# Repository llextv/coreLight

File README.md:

# CoreLight

CoreLight is an open-source DIY lighting controller built around an STM32H743.

The project is designed to manage stage lighting systems with up to **13 DMX universes**, Ethernet protocols such as **Art-Net and sACN**, timecode synchronization, show playback and system monitoring.

The goal is not to recreate a grandMA3 console. CoreLight is intended to be a hardware platform for a future open-source lighting-control system.

## Main features

- Up to 13 DMX outputs
- DMX512 and RS-485 communication
- Art-Net and sACN support
- Planned RDM support
- LTC and MTC timecode
- Show recording and playback
- Standalone operation
- DMX routing and merging
- Failover and redundancy
- Ethernet and OSC control
- Internal web interface
- Temperature, power and fan monitoring
- MicroSD and Flash storage
- USB-C for programming and updates
- RTC with battery backup
- Custom 4-layer PCB
- 3D-printed rack-mount enclosure

Most of these features are still under development. The current version should be considered a hardware prototype rather than a finished lighting controller.

---

## Architecture

The STM32H743 is the central processor of the system. It handles network communication, timecode, DMX processing, show playback and system monitoring.

The controller can also receive LTC, MTC and external event inputs. Lighting data is processed by the STM32 and sent to the required DMX outputs.

---

## Hardware

The current design uses the following main components:

| Component | Function |
|---|---|
| **STM32H743ZIT6** | Main microcontroller |
| **W5500** | Ethernet interface |
| **MAX3485** | DMX / RS-485 transceivers |
| **CD74HC4067M** | Signal routing and multiplexing |
| **IS42S16400J-7TL** | External SDRAM |
| **W25Q128JVSIQ** | SPI Flash |
| **DS3231M+** | Real-time clock |
| **INA226AIDGST** | Power monitoring |
| **TMP117AIDRVR** | Temperature monitoring |
| **SM712** | DMX transient protection |
| **USBLC6-2SC6** | USB ESD protection |

The complete component list is available in [BOM.csv](BOM.csv).

---

## Processing and memory

The STM32H743 was selected because the project requires more processing power and memory bandwidth than a basic microcontroller-based DMX interface.

It is responsible for:

- Art-Net, sACN and OSC communication
- DMX universe management
- RDM and DMX monitoring
- Show playback
- Timecode processing
- Failover logic
- Fan and thermal management
- System logs and diagnostics

### External SDRAM

The external SDRAM is used for temporary runtime data such as:

- DMX buffers
- Network packets
- Show playback data
- Large processing structures

### SPI Flash

The W25Q128JVSIQ Flash can be used for firmware, configuration and persistent system data.

### MicroSD card

The microSD card is intended for user-accessible files:

```text
/show
/config
/logs
/firmware
```

Shows, configuration files, logs and firmware updates can be stored on the card.

---

## DMX

CoreLight is designed to support up to **13 DMX universes**.

Each output uses a MAX3485 RS-485 transceiver and includes transient protection. A DMX universe contains up to 512 channels, giving a theoretical total of:

\[
13 \times 512 = 6656 \text{ DMX channels}
\]

Standard DMX wiring is used

The DMX data rate is 250 kbit/s.

Planned DMX features include:

- Flexible universe routing
- DMX repeater mode
- RDM
- DMX monitoring
- Signal-loss detection
- DMX merging and failover

For example, one network universe could be sent to several physical outputs

---

## Art-Net, sACN and Ethernet

Ethernet communication is handled by the W5500.

The network interface is intended to support:

- Art-Net
- sACN
- OSC
- Web-based configuration and monitoring

Network universes can be mapped to any of the physical DMX outputs instead of being permanently assigned to a single port.

---

## Timecode

CoreLight includes an LTC input and is designed to support MTC.

Timecode can be used to trigger lighting events or control show playback:

Example events could include scene changes, effect triggers or the start of a complete lighting sequence.

The RTC is used for system time, logs and scheduled events. It is separate from LTC, which is used for show synchronization.

---

## Standalone playback

A show can be uploaded to the microSD card and played back without a permanent computer connection.

A show file may contain:

- Scenes
- Cues
- DMX values
- Timing information
- Events
- Timecode positions

During playback, the STM32 loads the required data and generates the DMX output in real time.

---

## Failover and DMX merging

One of the main objectives is to improve system reliability during shows.

CoreLight is intended to detect problems such as:

- Loss of network data
- Software or hardware failure
- Missing DMX input
- Communication errors

Depending on the final firmware, the controller could switch to a backup source or continue playback using a locally stored show.

DMX merging is also planned, allowing several sources to contribute to the same output:

The merging rules and failover behavior are still being designed.

---

## Monitoring and cooling

The system includes temperature and power monitoring using a TMP117 and an INA226.

The firmware will be able to control the cooling fan and warn the user in case of excessive temperature or abnormal power consumption.

Available hardware includes:

- Temperature sensor
- Power monitor
- Fan output
- Status LEDs
- Buzzer

---

## Power supply

The controller is designed for a 24 V DC input.

The regulated voltages power the STM32, Ethernet interface, DMX transceivers, sensors and other logic circuits.

---

## User interface and web interface

The initial local interface consists of:

- Rotary encoder
- Push buttons
- Status LEDs
- Buzzer

A future web interface will provide access to:

- System status
- DMX monitoring
- Network settings
- Show management
- Logs
- Temperature and power data
- Firmware updates

The controller is intended to be configurable from a browser without requiring a dedicated screen.

Software link for the moment: 
https://www.qlcplus.org/download#

---

## PCB and enclosure

The PCB was designed in KiCad and uses four layers to simplify routing and provide dedicated ground and power planes.

The board contains:

- STM32H743
- External SDRAM
- SPI Flash
- Ethernet
- 13 DMX interfaces
- LTC input
- USB-C
- MicroSD
- RTC
- Power regulation
- Monitoring circuits
- User interface connections

The current design contains approximately 192 footprints.

The enclosure is a custom 3D-printed rack-mount case with openings for the DMX outputs, Ethernet, USB-C, LTC, power, fan and user controls.

Assembly file: [coreLightAssembly.step](cad/coreLightAssembly.step)

CAD files are available in:

```text
/cad
```

The complete KiCad schematic is available in:

```text
/scheme
```

---

## Estimated cost

The current estimate is:

```text
Components:  $66.01
PCB:         $36.99
Total:      ~$103 USD
```

This does not include shipping, assembly, enclosure parts or future design changes.

---

## Project journal

The development process is documented in [JOURNAL.md](JOURNAL.md).

It includes the PCB design, STM32CubeMX configuration, KiCad work, enclosure design, BOM creation and the problems encountered during development.

---

## Inspiration

CoreLight was inspired by professional lighting hardware such as the grandMA3 Processing Unit and Replay Unit.

The project is independent and is not affiliated with MA Lighting.

- [MA Lighting grandMA3 Processing Unit](https://www.malighting.com/product/grandma3-processing-unit-m-4010510/)
- [MA Lighting grandMA3 Replay Unit](https://www.malighting.com/product/grandma3-replay-unit-4010507/)

---

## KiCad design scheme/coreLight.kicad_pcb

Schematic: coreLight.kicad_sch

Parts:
BT1: Battery; BatteryHolder_Keystone_3000_1x12mm
BZ1: Buzzer 3.3V; Buzzer_12x9.5RM7.6
C1, C4, C6, C9, C13, C16, C27, C29, C30, C31, C34, C36, C39, C42, C44, C46, C48, C50, C52, C54, C56, C58, C60, C62, C64, C66, C68, C69, C71, C72, C76, C78, C79: 100nF; C_0805_2012Metric
C2, C3, C32, C33: 22pF; C_0805_2012Metric
C5, C7, C8, C28, C35, C40, C41, C43, C45, C47, C49, C51, C53, C55, C57, C59, C61, C63, C65, C75, C77: 4.7µF; C_0805_2012Metric
C12, C81: 1uF; C_0805_2012Metric
C26, C70: 10uF; C_0805_2012Metric
C37, C67: 4.7uF; C_0805_2012Metric
C73, C74: 10nF; C_0805_2012Metric
C80: 2.2nF; C_0805_2012Metric
D4: D_TVS_Dual_AAC; D_SOT-23
D17: 1N5819; D_DO-41_SOD81_P10.16mm_Horizontal
D31, D33, D34, D35, D36, D37, D38, D39, D40, D41, D42, D43, D44: SM712; D_SOT-23
D32: 1N4148; D_DO-35_SOD27_P7.62mm_Horizontal
D47, D48, D49, D50, D51, D52, D53: LED; LED_0805_2012Metric
F2: Fuse 3-5A; Fuse_1812_4532Metric_Pad1.30x3.40mm_HandSolder
FB1, FB3: FerriteBead; C_0805_2012Metric
J1: Micro_SD_Card; microSD_HC_Hirose_DM3D-SF
J3: RJ45_Hanrun_HR911105A_Horizontal
J5, J6, J21, J23, J24, J25, J26, J27, J28, J29, J30, J31, J32: Con DMX; JST_XH_B3B-XH-A_1x03_P2.50mm_Vertical
J16: USB_C_Receptacle_USB2.0_16P; USB_C_Receptacle_HRO_TYPE-C-31-M-12
J17: 24v in; TerminalBlock_Phoenix_MKDS-1,5-2-5.08_1x02_P5.08mm_Horizont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
J18: FAN; JST_XH_B2B-XH-A_1x02_P2.50mm_Vertical
J19: SWD; JST_XH_B5B-XH-A_1x05_P2.50mm_Vertical
J20: UART; JST_XH_B4B-XH-A_1x04_P2.50mm_Vertical
J22: LTC IN; Jack_3.5mm_Ledino_KB3SPRS_Horizontal
Q14, Q16: MOSFET; TO-252-3_TabPin2
Q15: 2N7002/AOD; Q_SOT-23
R1, R4, R5, R6, R9, R42, R58, R74, R80, R82, R83, R84, R88, R89, R90: 10k; R_0805_2012Metric
R2, R3, R10, R11, R12, R13, R14, R15, R16: 330R; R_0805_2012Metric
R7: 12.1k; R_0805_2012Metric
R8: 12.4k; R_0805_2012Metric
R41: 1k; R_0805_2012Metric
R43, R44: 5.1K; R_0805_2012Metric
R45: 10-50mΩ; R_0805_2012Metric
R59, R72, R75, R85, R86: 100k; R_0805_2012Metric
R73: 52.3k; R_0805_2012Metric
R76: 100R; R_0805_2012Metric
R87: 120R; R_0805_2012Metric
SW1: BOOT; SW_Push_1P1T_NO_6x6mm_H9.5mm
SW2: EC11 with BTN; RotaryEncoder_Alps_EC11E-Switch_Vertical_H20mm
SW3, SW4, SW5, SW6, SW7: SW_Push; SW_Push_1P1T_NO_6x6mm_H9.5mm
U2: IS42S16400J-xC; TSOP-II-54_22.2x10.16mm_P0.8mm
U3: W25Q128JVS; SOIC-8_5.23x5.23mm_P1.27mm
U4: NUCLEO144-H743ZI; LQFP-144-1EP_20x20mm_P0.5mm_EP6.5x6.5mm
U5: W5500; LQFP-48_7x7mm_P0.5mm
U6, U7, U8, U9, U10, U11, U12, U13, U14, U15, U16, U17, U18, U27: MAX3485; SOIC-8_3.9x4.9mm_P1.27mm
U19: DS3231M; SOIC-16W_7.5x10.3mm_P1.27mm
U20: LM2596S-ADJ 5V; TO-263-5_TabPin3
U21: AP2112K-3.3; SOT-23-5
U22: INA226; VSSOP-10_3x3mm_P0.5mm
U23, U24: TMP117xxDRV; WSON-6-1EP_2x2mm_P0.65mm_EP1x1.6mm
U25: CD74HC4067M; SOIC-24W_7.5x15.4mm_P1.27mm
U26: USBLC6-2SC6; SOT-23-6
Y1, Y3: Crystal 25MHz; Crystal_SMD_3225-4Pin_3.2x2.5mm

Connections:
+3.3V: BZ1.1 (+), C1.2, C4.1, C5.1, C6.1, C7.1, C8.1, C9.1, C26.2, C27.2, C28.1, C29.1, C30.1, C31.1, C34.1, C37.2, C39.1, C40.1, C41.1, C42.1, C43.1, C44.1, C45.1, C46.1, C47.1, C48.1, C49.1, C50.1, C51.1, C52.1, C53.1, C54.1, C55.1, C56.1, C57.1, C58.1, C59.1, C60.1, C61.1, C62.1, C63.1, C64.1, C67.1, C68.1, C69.1, C70.1, C71.1, C75.1, C76.1, C77.1, C78.1, C79.1, D32.1 (K), FB1.2, FB3.2, J1.4 (VDD), J3.4 (TCT), J3.5 (RCT), J19.1, J20.1, R1.1, R10.1, R11.1, R12.1, R13.1, R14.1, R15.2, R16.2, R42.2, R58.2, R89.2, R90.2, SW1.1, U2.1 (VDD), U2.3 (VDDQ), U2.9 (VDDQ), U2.14 (VDD), U2.27 (VDD), U2.43 (VDDQ), U2.49 (VDDQ), U3.8 (VCC), U4.5 (VDD), U4.33 (VBAT), U5.4 (AVDD), U5.8 (AVDD), U5.11 (AVDD), U5.15 (AVDD), U5.17 (AVDD), U5.21 (AVDD), U5.28 (VDD), U6.8 (VCC), U7.8 (VCC), U8.8 (VCC), U9.8 (VCC), U10.8 (VCC), U11.8 (VCC), U12.8 (VCC), U13.8 (VCC), U14.8 (VCC), U15.8 (VCC), U16.8 (VCC), U17.8 (VCC), U18.8 (VCC), U19.2 (VCC), U22.6 (VS), U23.5 (V+), U24.4 (ADD0), U24.5 (V+), U25.24 (VCC), U27.8 (VCC)
+5V: C65.1, C66.1, R73.2, R75.1, U20.2 (OUT), U21.1 (VIN)
+24V_LOAD: C35.1, C36.1, J18.1, R45.2, R72.2, U20.1 (VIN), U22.9 (Vin-)
+24V_SAFE: Q14.2 (S), R45.1, U22.8 (Vbus), U22.10 (Vin+)
BTN_1: SW3.1, U4.47 (PE3)
BTN_2: SW4.1, U4.48 (PE4)
BTN_3: SW7.1, U4.50 (PE5)
BTN_4: SW6.1, U4.62 (PE6)
BTN_5: SW5.1, U4.23 (BT/PC13)
BUZZER_CTRL: R41.1, U4.96 (PB1)
DMX_EN_1: U4.105 (USB_ID/PA10), U18.2 (~RE), U18.3 (DE)
DMX_EN_2: U4.17 (PA15), U17.2 (~RE), U17.3 (DE)
DMX_EN_3: U4.40 (PD3), U8.2 (~RE), U8.3 (DE)
DMX_EN_4: U4.39 (PD4), U11.2 (~RE), U11.3 (DE)
DMX_EN_5: U4.43 (PD6), U14.2 (~RE), U14.3 (DE)
DMX_EN_6: U4.45 (PD7), U16.2 (~RE), U16.3 (DE)
DMX_EN_7: U4.63 (PG9), U7.2 (~RE), U7.3 (DE)
DMX_EN_8: U4.66 (PG10), U10.2 (~RE), U10.3 (DE)
DMX_EN_9: U4.133 (PG14), U13.2 (~RE), U13.3 (DE)
DMX_EN_10: U4.103 (SWO/PB3), U15.2 (~RE), U15.3 (DE)
DMX_EN_11: U4.99 (PB4), U6.2 (~RE), U6.3 (DE)
DMX_EN_12: U4.101 (PB5), U9.2 (~RE), U9.3 (DE)
DMX_EN_13: U4.77 (PB9), U12.2 (~RE), U12.3 (DE)
DMX_RX_1: U4.98 (PB15), U18.1 (RO)
DMX_RX_2: U4.109 (PA3), U17.1 (RO)
DMX_RX_3: U4.90 (PB11), U8.1 (RO)
DMX_RX_4: U4.30 (ETH_MDIO/PA1), U11.1 (RO)
DMX_RX_5: U4.88 (PB12), U14.1 (RO)
DMX_RX_6: U16.1 (RO), U25.8 (I1)
DMX_RX_7: U7.1 (RO), U25.6 (I3)
DMX_RX_8: U10.1 (RO), U25.4 (I5)
DMX_RX_9: U13.1 (RO), U25.2 (I7)
DMX_RX_10: U15.1 (RO), U25.22 (I9)
DMX_RX_11: U6.1 (RO), U25.20 (I11)
DMX_RX_12: U9.1 (RO), U25.18 (I13)
DMX_RX_13: U12.1 (RO), U25.16 (I15)
DMX_TX_1: U4.100 (LD3/PB14), U18.4 (DI)
DMX_TX_2: U4.107 (PA2), U17.4 (DI)
DMX_TX_3: U4.97 (PB10), U8.4 (DI)
DMX_TX_4: U4.28 (ETH_REF_CLK/PA0), U11.4 (DI)
DMX_TX_5: U4.89 (PB6), U14.4 (DI)
DMX_TX_6: U16.4 (DI), U25.9 (I0)
DMX_TX_7: U7.4 (DI), U25.7 (I2)
DMX_TX_8: U10.4 (DI), U25.5 (I4)
DMX_TX_9: U13.4 (DI), U25.3 (I6)
DMX_TX_10: U15.4 (DI), U25.23 (I8)
DMX_TX_11: U6.4 (DI), U25.21 (I10)
DMX_TX_12: U9.4 (DI), U25.19 (I12)
DMX_TX_13: U12.4 (DI), U25.17 (I14)
ENC_A: C73.1, R42.1, SW2.A, U4.25 (RTC_CRYSTAL/PC14)
ENC_B: C74.1, R58.1, SW2.B, U4.27 (RTC_CRYSTAL/PC15)
ENC_BTN: SW2.S1
ETH_CS: U4.41 (PD5), U5.32 (~SCS)
ETH_INT: U4.65 (PG12), U5.36 (~INT)
ETH_MISO: U4.35 (PC2), U5.34 (MISO)
ETH_MOSI: U4.36 (ETH_MDC/PC1), U5.35 (MOSI)
ETH_RST: U4.70 (PG11/ETH_TX_EN), U5.37 (~RST)
ETH_SCK: U4.102 (ETH_TXD1/PB13), U5.33 (SCLK)
FAN_PWM: R76.2, R86.2, U4.94 (PB2)
FMC_A0: U2.23 (A0), U4.53 (PF0)
FMC_A1: U2.24 (A1), U4.51 (PF1)
FMC_A2: U2.25 (A2), U4.52 (PF2)
FMC_A3: U2.26 (A3), U4.130 (PF3)
FMC_A4: U2.29 (A4), U4.110 (PF4)
FMC_A5: U2.30 (A5), U4.108 (PF5)
FMC_A6: U2.31 (A6), U4.131 (PF12)
FMC_A7: U2.32 (A7), U4.129 (PF13)
FMC_A8: U2.33 (A8), U4.122 (PF14)
FMC_A9: U2.34 (A9), U4.132 (PF15)
FMC_A10: U2.22 (A10), U4.59 (PG0)
FMC_A11: U2.35 (A11), U4.58 (PG1)
FMC_BA0: U2.20 (BA0), U4.141 (PG4)
FMC_BA1: U2.21 (BA1), U4.140 (PG5)
FMC_D0: U2.2 (DQ0), U4.118 (PD14)
FMC_D1: U2.4 (DQ1), U4.120 (PD15)
FMC_D2: U2.5 (DQ2), U4.57 (PD0)
FMC_D3: U2.7 (DQ3), U4.55 (PD1)
FMC_D4: U2.8 (DQ4), U4.116 (PE7)
FMC_D5: U2.10 (DQ5), U4.112 (PE8)
FMC_D6: U2.11 (DQ6), U4.124 (PE9)
FMC_D7: U2.13 (DQ7), U4.119 (PE10)
FMC_D8: U2.42 (DQ8), U4.128 (PE11)
FMC_D9: U2.44 (DQ9), U4.121 (PE12)
FMC_D10: U2.45 (DQ10), U4.127 (PE13)
FMC_D11: U2.47 (DQ11), U4.123 (PE14)
FMC_D12: U2.48 (DQ12), U4.125 (PE15)
FMC_D13: U2.50 (DQ13), U4.82 (STLINK_TX/PD8)
FMC_D14: U2.51 (DQ14), U4.69 (STLINK_RX/PD9)
FMC_D15: U2.53 (DQ15), U4.137 (PD10)
FMC_NBL0: U2.15 (LDQM), U4.136 (PE0)
FMC_NBL1: U2.39 (UDQM), U4.61 (PE1)
FMC_SDCAS: U2.17 (~CAS), U4.64 (PG15)
FMC_SDCKE0: U2.37 (CKE), U4.37 (PC3)
FMC_SDCLK: U2.38 (CLK), U4.138 (PG8)
FMC_SDNE0: U2.19 (~CS), U4.106 (ETH_RXD0/PC4)
FMC_SDNWE: U2.16 (~WE), U4.38 (PC0)
FMC_SDRAS: U2.18 (~RAS), U4.134 (PF11)
GND: BT1.2 (-), C1.1, C2.1, C3.2, C4.2, C5.2, C6.2, C7.2, C8.2, C9.2, C12.2, C13.2, C16.1, C26.1, C27.1, C28.2, C29.2, C30.2, C31.2, C32.1, C33.2, C34.2, C35.2, C36.2, C37.1, C39.2, C40.2, C41.2, C42.2, C43.2, C44.2, C45.2, C46.2, C47.2, C48.2, C49.2, C50.2, C51.2, C52.2, C53.2, C54.2, C55.2, C56.2, C57.2, C58.2, C59.2, C60.2, C61.2, C62.2, C63.2, C64.2, C65.2, C66.2, C67.2, C68.2, C69.2, C70.2, C71.2, C72.1, C73.2, C74.2, C75.2, C76.2, C77.2, C78.2, C79.2, C80.1, C81.2, D4.3 (common), D31.3 (common), D33.3 (common), D34.3 (common), D35.3 (common), D36.3 (common), D37.3 (common), D38.3 (common), D39.3 (common), D40.3 (common), D41.3 (common), D42.3 (common), D43.3 (common), D44.3 (common), J1.6 (VSS), J1.9 (SHIELD), J3.10, J3.11, J5.1, J6.1, J16.A1 (GND), J16.A12 (GND), J16.B1 (GND), J16.B12 (GND), J16.S1 (SHIELD), J17.2, J19.3, J20.4, J21.1, J22.S, J23.1, J24.1, J25.1, J26.1, J27.1, J28.1, J29.1, J30.1, J31.1, J32.1, Q15.3 (D), Q16.2 (S), R4.1, R5.1, R6.1, R7.2, R8.2, R9.1, R43.2, R44.2, R59.2, R74.1, R85.1, R86.1, SW2.C, SW2.S2, SW3.2, SW4.2, SW5.2, SW6.2, SW7.2, U2.6 (GNDQ), U2.12 (GNDQ), U2.28 (GND), U2.41 (GND), U2.46 (GNDQ), U2.52 (GNDQ), U2.54 (GND), U3.4 (GND), U4.8 (GND), U4.19 (GND), U4.20 (GND), U4.22 (GND), U4.49 (GND), U4.60 (GND), U4.71 (GND), U4.72 (GND), U4.81 (GND), U4.92 (GND), U4.104 (AGND), U4.111 (GND), U4.126 (GND), U4.135 (GND), U4.143 (GND), U4.144 (GND), U5.3 (AGND), U5.9 (AGND), U5.14 (AGND), U5.16 (AGND), U5.19 (AGND), U5.29 (GND), U5.48 (AGND), U6.5 (GND), U7.5 (GND), U8.5 (GND), U9.5 (GND), U11.5 (GND), U12.5 (GND), U13.5 (GND), U14.5 (GND), U15.5 (GND), U16.5 (GND), U17.5 (GND), U18.5 (GND), U19.5 (GND), U19.6 (GND), U19.7 (GND), U19.8 (GND), U19.9 (GND), U19.10 (GND), U19.11 (GND), U19.12 (GND), U19.13 (GND), U20.3 (GND), U21.2 (GND), U22.1 (A1), U22.2 (A0), U22.7 (GND), U23.2 (GND), U23.4 (ADD0), U24.2 (GND), U25.12 (GND), U25.15 (~E), U26.2 (GND), U27.2 (~RE), U27.3 (DE), U27.4 (DI), U27.5 (GND)
I2C_SCL: U4.75 (PB8), U19.16 (SCL), U22.5 (SCL), U23.1 (SCL), U24.1 (SCL)
I2C_SDA: U4.21 (LD2/PB7), U19.15 (SDA), U22.4 (SDA), U23.6 (SDA), U24.6 (SDA)
LED_STATUS1: D53.1 (K), U4.117 (PD11)
LED_STATUS2: D51.1 (K), U4.115 (PD12)
LED_STATUS3: D52.1 (K), U4.113 (PD13)
LED_STATUS4: D49.1 (K), U4.42 (PG2)
LED_STATUS5: D50.1 (K), U4.44 (PG3)
LED_STATUS6: D48.1 (K), U4.139 (PG7/USB_GPIO_IN)
LED_STATUS7: D47.1 (K), U4.93 (USB_VBUS/PA9)
LTC_RX: U4.87 (ETH_CRS_DV/PA7), U27.1 (RO)
MUX_S0: U4.32 (PA4), U25.10 (S0)
MUX_S1: U4.83 (PA5), U25.11 (S1)
MUX_S2: U4.85 (PA6), U25.14 (S2)
MUX_S3: U4.34 (PB0), U25.13 (S3)
unnamed: BT1.1 (+), D17.2 (A)
unnamed: BZ1.2 (-), D32.2 (A), Q16.3 (D)
unnamed: D4.1 (A1), J22.T, R87.1, U27.6 (A)
unnamed: D4.2 (A2), J22.R, R87.2, U27.7 (B)
unnamed: D17.1 (K), U19.14 (VBAT)
unnamed: D31.1 (A1), J6.3, U18.6 (A)
unnamed: D31.2 (A2), J6.2, U18.7 (B)
unnamed: D33.1 (A1), J5.3, U17.6 (A)
unnamed: D33.2 (A2), J5.2, U17.7 (B)
unnamed: D34.1 (A1), J21.3, U8.6 (A)
unnamed: D34.2 (A2), J21.2, U8.7 (B)
unnamed: D35.1 (A1), J23.3, U11.6 (A)
unnamed: D35.2 (A2), J23.2, U11.7 (B)
unnamed: D36.1 (A1), J24.3, U14.6 (A)
unnamed: D36.2 (A2), J24.2, U14.7 (B)
unnamed: D37.1 (A1), J25.3, U16.6 (A)
unnamed: D37.2 (A2), J25.2, U16.7 (B)
unnamed: D38.1 (A1), J26.3, U7.6 (A)
unnamed: D38.2 (A2), J26.2, U7.7 (B)
unnamed: D39.1 (A1), J27.3, U10.6 (A)
unnamed: D39.2 (A2), J27.2, U10.7 (B)
unnamed: D40.1 (A1), J28.3, U13.6 (A)
unnamed: D40.2 (A2), J28.2, U13.7 (B)
unnamed: D41.1 (A1), J29.3, U15.6 (A)
unnamed: D41.2 (A2), J29.2, U15.7 (B)
unnamed: D42.1 (A1), J30.3, U6.6 (A)
unnamed: D42.2 (A2), J30.2, U6.7 (B)
unnamed: D43.1 (A1), J31.3, U9.6 (A)
unnamed: D43.2 (A2), J31.2, U9.7 (B)
unnamed: D44.1 (A1), J32.3, U12.6 (A)
unnamed: D44.2 (A2), J32.2, U12.7 (B)
unnamed: D47.2 (A), R16.1
unnamed: D48.2 (A), R15.1
unnamed: D49.2 (A), R13.2
unnamed: D50.2 (A), R14.2
unnamed: D51.2 (A), R11.2
unnamed: D52.2 (A), R12.2
unnamed: D53.2 (A), R10.2
unnamed: J1.3 (CMD), R88.2
unnamed: J1.7 (DAT0), R83.2
unnamed: J1.8 (DAT1), R84.2
unnamed: J1.1 (DAT2), R80.2
unnamed: J1.2 (DAT3/CD), R82.2
unnamed: J3.9, R2.1
unnamed: J3.12, R3.1
unnamed: J3.3 (RD+), U5.5 (RXN)
unnamed: J3.6 (RD-), U5.6 (RXP)
unnamed: J3.1 (TD+), U5.1 (TXN)
unnamed: J3.2 (TD-), U5.2 (TXP)
unnamed: J16.A5 (CC1), R44.1
unnamed: J16.B5 (CC2), R43.1
unnamed: J16.A6 (D+), J16.B6 (D+), U26.1 (I/O1)
unnamed: J16.A7 (D-), J16.B7 (D-), U26.3 (I/O2)
unnamed: F2.2, J17.1
unnamed: J18.2, Q15.2 (S)
unnamed: F2.1, Q14.3 (D)
unnamed: Q14.1 (G), R85.2
unnamed: Q15.1 (G), R76.1
unnamed: Q16.1 (G), R41.2, R59.1
unnamed: C12.1, C13.1, FB3.1, U4.79 (AVDD)
unnamed: C3.1, U4.29 (PH0), Y1.2
unnamed: C2.2, U4.31 (PH1), Y1.1
unnamed: R9.2, SW1.2, U4.7 (~BOOT0)
unnamed: R1.2, U4.14 (~RST)
unnamed: C81.1, U5.22 (1V2O)
unnamed: R2.2, U5.27 (ACTLED)
unnamed: R7.1, U5.10 (EXRES1)
unnamed: R3.2, U5.25 (LINKLED)
unnamed: R4.2, U5.45 (PMODE0)
unnamed: R5.2, U5.44 (PMODE1)
unnamed: R6.2, U5.43 (PMODE2)
unnamed: C80.2, U5.20 (TOCAP)
unnamed: R8.1, U5.18 (VBG)
unnamed: C33.1, U5.30 (XI/CLKIN), Y3.2
unnamed: C32.2, U5.31 (XO), Y3.1
unnamed: R89.1, U19.3 (~INT/SQW)
unnamed: R90.1, U19.4 (~RST)
unnamed: R73.1, R74.2, U20.4 (FB)
unnamed: R72.1, U20.5 (~ON/OFF)
unnamed: R75.2, U21.3 (EN)
unnamed: C16.2, FB1.1, U21.5 (VOUT)
QSPI_BK1_IO0: U3.5 (DI(IO0)), U4.54 (PF8)
QSPI_BK1_IO1: U3.2 (DO(IO1)), U4.56 (PF9)
QSPI_BK1_IO2: U3.3 (IO2), U4.46 (PE2)
QSPI_BK1_IO3: U3.7 (IO3), U4.9 (PF6)
QSPI_BK1_NCS: U3.1 (~CS), U4.142 (PG6/USB_GPIO_OUT)
QSPI_CLK: U3.6 (CLK), U4.114 (PF10)
SDIO_CK: J1.5 (CLK)
SDIO_CMD: R88.1, U4.4 (PD2)
SDIO_D0: R83.1, U4.74 (PC8)
SDIO_D1: R84.1, U4.73 (PC9)
SDIO_D2: R80.1, U4.1 (PC10)
SDIO_D3: R82.1, U4.2 (PC11)
SYS_RST: C72.2, J19.5
SYS_SWCLK: J19.2, U4.15 (TCK/PA14)
SYS_SWDIO: J19.4, U4.13 (TMS/PA13)
UART_RX: J20.3
UART_TX: J20.2
UART_TX_MULTIPLEXER: U4.76 (PC6), U25.1 (COM)
USB_DM: U4.86 (USB_DM/PA11), U26.4 (I/O2)
USB_DP: U4.84 (USB_DP/PA12), U26.6 (I/O1)
USB_VBUS: J16.A4 (VBUS), J16.A9 (VBUS), J16.B4 (VBUS), J16.B9 (VBUS), U26.5 (VBUS)

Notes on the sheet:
DEBUG
BRAIN
5V -> 3.3V
USB-C
DMX
MEMORY
LTC
MESURE ALIM
RTC
SENSORS
24V -> 5V
INPUT
ETHERNET
POWER

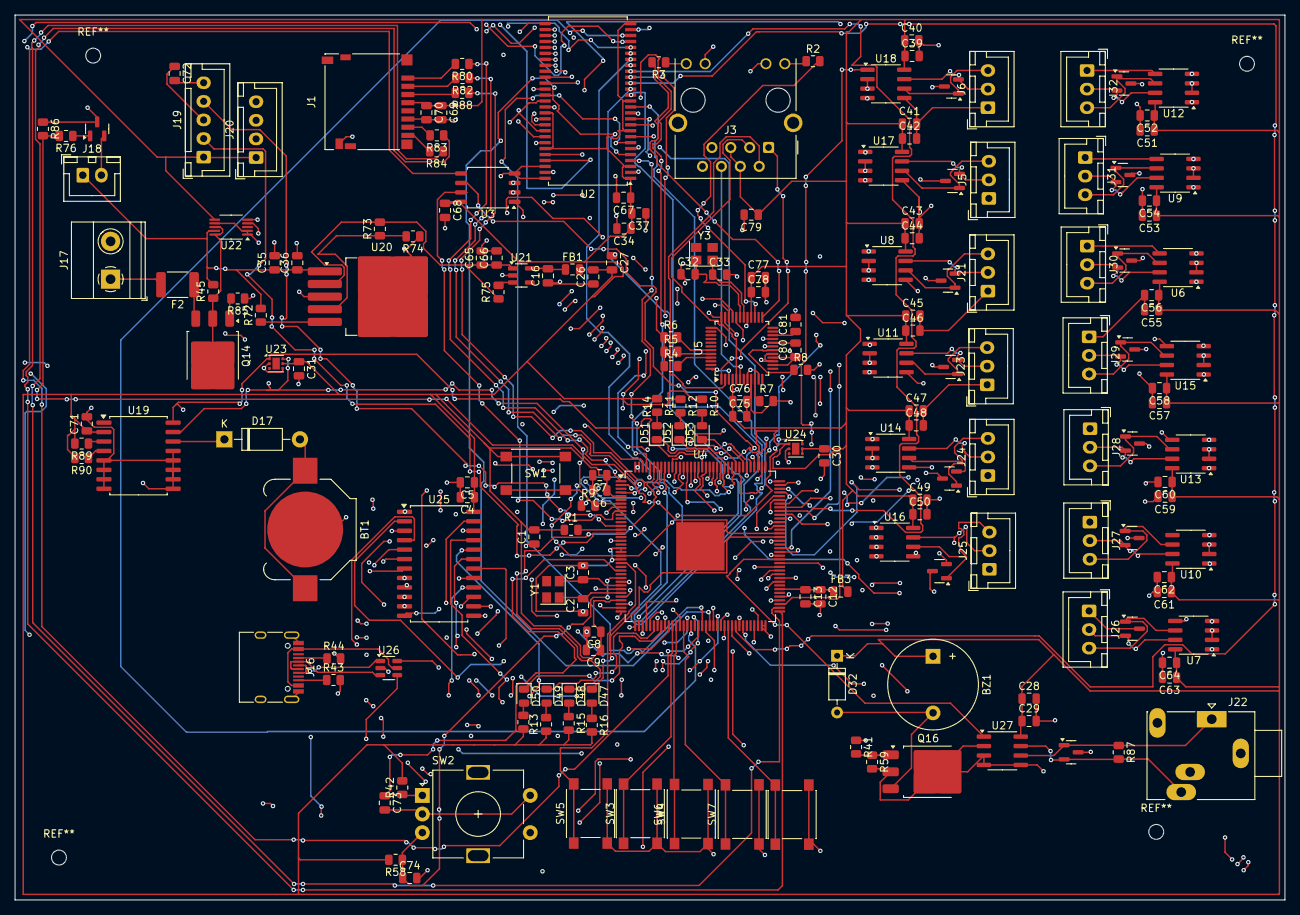
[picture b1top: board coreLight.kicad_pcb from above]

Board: 4 copper layers, 170.7 x 119.0 mm, 192 parts (0 on the bottom side), 210 nets.
